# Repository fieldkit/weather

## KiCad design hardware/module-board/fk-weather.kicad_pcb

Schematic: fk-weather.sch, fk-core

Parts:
BT1: BATTERY_CELL; BAT_CR1210
C1, C2: 18pF; CAP-0603
C3, C4, C6, C7, C8, C13, C16, C18, C20: 100nF; CAP-0603
C5, C11, C12: 1uF; CAP-0603
C9, C14: 4.7uF; CAP-0603
C10: 4.7nF; CAP-0603
C15, C21: 10uF; CAP-0603
C17, C19: 10nF; CAP-0603
D1: Green; LED-0603
D4: PRTR5V0U2X; SOT-143B
D5: Orange; LED-0603
D6, D7, D8, D9, D10, D11: DIODE; SOD-123
F1: MF-PSMF050X-2; MF-PSMF020X
J1: MICRO-USB; USB_1051330011
J2, J7: CONN_01x05; Molex_CLIK-Mate_502382-0570_1x05_P1.25mm_Vertical
J3: CONN_01x03_SERIAL; Molex_CLIK-Mate_502382-0370_1x03_P1.25mm_Vertical
J4: CONN_01x04; Molex_CLIK-Mate_502382-0470_1x04_P1.25mm_Vertical
J5: MICRO-USB; USB_10118193-0001LF-core-mod
J6: CONN_02x05_SWD; HDR_02x05_Pitch1.27mm_SMD_SWD
J8: CONN_01x04; BM04B-SRSS-TB
J9, J12: CONN_01x02; SJ_OPEN
J10, J11: CONN_01x06; WURTH_615006138421
L1, L2: BLM18KG221SN1D; IND-0603
M1, M2, M3, M4: MOUNT_HOLE; HOLE_NPTH_2.7MM
Q4: 2N7002LT1G; SOT-23
R1, R22, R23, R30, R31, R32, R33: 1K; RES-0603
R2, R9: 330R; RES-0603
R3, R17: 2k2; RES-0603
R4, R5, R12: 10K; RES-0603
R6, R7, R16, R18, R19, R20, R34: 4.7K; RES-0603
R8, R14, R15: 100K; RES-0603
R10: 1M; RES-0603
R11, R13: ?; RES-0603
SW1: SPNO; SW_SPST_WURTH_1
U1: ATSAMD21G18A-AU; TQFP-48_7x7mm_Pitch0.5mm
U2: MCP1700T-3302E/MB; SOT-89
U3: TPS2052B; SOIC-8-N
U4: S25FL116K0XMFI041; SOIC-8-N-WIDE
U5: SK6812
U6: PCF8523; SOIC-8-N
Y1, Y2: FC-135; ABS07

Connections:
3V3: C3.1, C7.1, C8.1, C12.1, C16.1, C17.1, D1.2 (A), D5.2 (A), J2.1, J4.1, J6.1, J7.1, J8.2, J9.1, J12.1, L2.2, R1.1, R4.1, R5.2, R6.2, R7.2, R8.1, R12.2, R16.2, R18.2, R19.2, R20.2, U1.17 (VDDIO), U1.36 (VDDIO), U1.44 (VDDIN), U2.3 (VOUT), U3.2, U5.3 (VDD), U6.8 (VDD)
5V0: C9.1, C11.1, L1.1, U2.2 (VIN)
/A0: U1.3 (PA02)
/A1_WIND_DIR: D8.1 (K), D9.2 (A), R30.2, R34.2, U1.7 (PB08)
/A3: U1.9 (PA04), U5.2 (DI)
/A4: U1.10 (PA05)
/A5: U1.47 (PB02)
/ATN: U1.22 (PA13)
/D0: U1.16 (PA11)
/D1: U1.15 (PA10)
/D2: U1.23 (PA14)
/D5_FLASH_CS: U1.24 (PA15), U4.1 (~CS~)
/D6_RAIN: D6.2 (A), D7.1 (K), R32.2, U1.29 (PA20)
/D7_WEATHER_EN: R11.1, U1.30 (PA21), U3.3
/D8_PERIPH_EN: R13.1, U1.11 (PA06), U3.4
/D9: U1.12 (PA07)
/D10_WIND_SPEED: D10.2 (A), D11.1 (K), R33.2, U1.27 (PA18)
/D12: U1.28 (PA19)
/D13: Q4.1 (G), U1.26 (PA17)
/D30: J3.3 (D30), U1.37 (PB22)
/D31: J3.2 (D31), U1.38 (PB23)
/MISO: U1.21 (PA12), U4.2 (SO/IO1)
/MOSI: U1.19 (PB10), U4.5 (SI/IO0)
/PERIPH_3V3: C18.1, C20.1, C21.1, J9.2, R14.1, U3.6, U4.3 (~WP~/IO2), U4.7 (~HOLD~/IO3), U4.8 (VCC)
/RAIN_2: J10.2
/RAIN_5: J10.5
/RESET: R2.1, U1.40 (RESETN)
/RST: J6.10, R2.2, R4.2, SW1.2; also elsewhere on the board
/RX_LED: U1.48 (PB03)
/SCK: U1.20 (PB11), U4.6 (SCLK)
/SCL1: J4.3, J8.4, R7.1, R20.1, U1.32 (PA23), U6.6 (SCL)
/SCL2: J2.4, J7.4, R18.1, U1.14 (PA09)
/SDA1: J4.4, J8.3, R6.1, R19.1, U1.31 (PA22), U6.5 (SDA)
/SDA2: J2.5, J7.5, R16.1, U1.13 (PA08)
/SWCLK: J6.4, U1.45 (PA30)
/SWDIO: J6.2, U1.46 (PA31)
/TX_LED: U1.39 (PA27)
/USB+: D4.2, J1.3 (D+), J5.3 (D+), U1.34 (PA25)
/USB-: D4.3, J1.2 (D-), J5.2 (D-), U1.33 (PA24)
/USB_ID: R9.2, U1.41 (PA28)
/WEATHER_3V3: C13.1, C15.1, D6.1 (K), D9.1 (K), D10.1 (K), J12.2, R15.1, R34.1, U3.7
GND: BT1.2 (-), C1.1, C2.1, C3.2, C4.2, C5.2, C6.2, C7.2, C8.2, C9.2, C10.2, C11.2, C12.2, C13.2, C14.2, C15.2, C16.2, C17.2, C18.2, C19.2, C20.2, C21.2, D4.1, D7.2 (A), D8.2 (A), D11.2 (A), J1.5 (GND), J2.2, J3.1 (GND), J4.2, J5.5 (GND), J6.3, J6.5, J6.9, J7.2, J8.1, Q4.2 (S), R3.2, R10.2, R11.2, R13.2, R14.2, R15.2, R22.2, R23.2, R31.2, SW1.1, U1.5 (GNDANA), U1.18 (GND), U1.35 (GND), U1.42 (GND), U2.1 (GND), U3.1, U4.4 (VSS), U5.1 (GND), U6.4 (VSS); also elsewhere on the board
unnamed: BT1.1 (+), U6.3 (VBAT)
unnamed: C1.2, U1.2 (PA01), Y1.1
unnamed: C2.2, U1.1 (PA00), Y1.2
unnamed: C4.1, L2.1, U1.6 (VDDANA)
unnamed: C5.1, U1.43 (VDDCORE)
unnamed: C10.1, J1.6 (SHIELD), J5.7 (SHIELD), R10.1
unnamed: C6.1, C14.1, U1.4 (PA03)
unnamed: C19.1, R1.2
unnamed: D1.1 (K), R3.1
unnamed: D5.1 (K), R17.1
unnamed: F1.1, L1.2
unnamed: J1.4 (ID), J5.4 (ID), R8.2, R9.1
unnamed: J10.3, R23.1
unnamed: J10.4, R32.1
unnamed: J11.2, R22.1
unnamed: J11.3, R31.1
unnamed: J11.4, R33.1
unnamed: J11.5, R30.1
unnamed: Q4.3 (D), R17.2
unnamed: R5.1, U3.8
unnamed: R12.1, U3.5
unnamed: U6.1 (XI), Y2.2
unnamed: U6.2 (XO), Y2.1
VUSB: D4.4, F1.2, J1.1 (VBUS), J5.1 (VBUS)

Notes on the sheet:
TX0
RX0
32.768kHz
12.5pF
USB / POWER MANAGEMENT
LEDs
MCU
I2C
EXTERNAL SENSOR
RAIN
WIND
RTC
MOUNTING
FLASH
CORE CONNECTOR
EXTERNAL SERIAL
PERIPHERALS

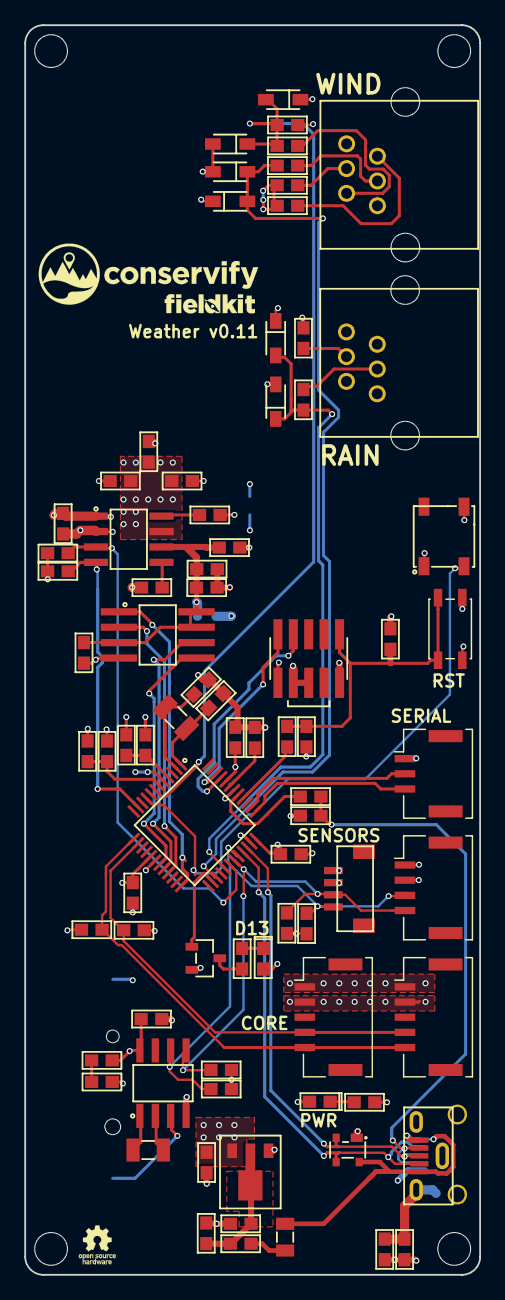
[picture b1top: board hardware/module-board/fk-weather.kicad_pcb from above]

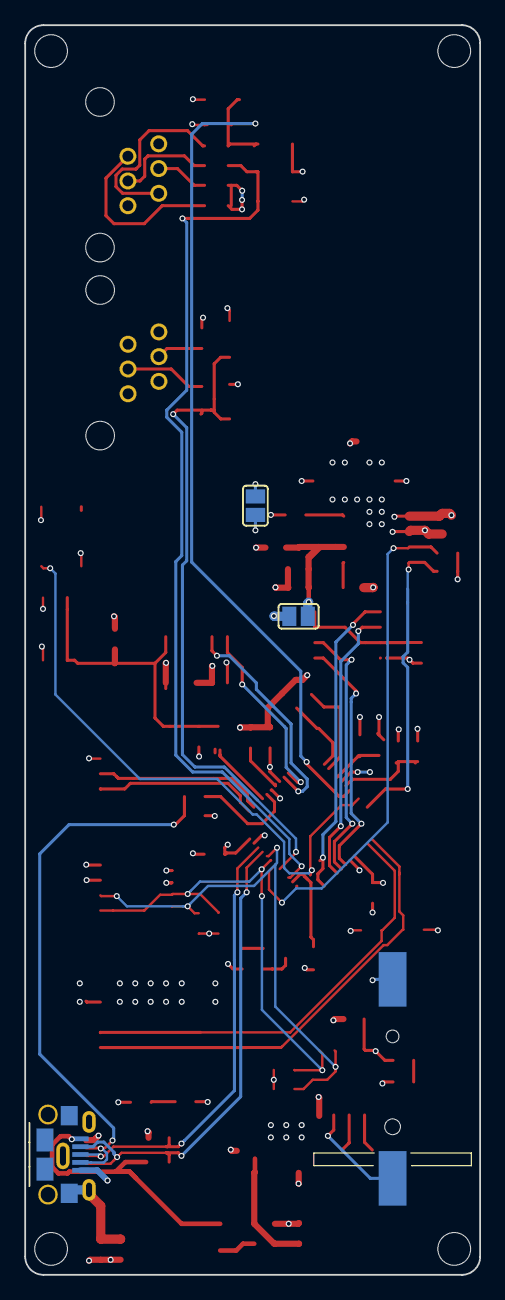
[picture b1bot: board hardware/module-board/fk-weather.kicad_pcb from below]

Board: 4 copper layers, 37.5 x 103.0 mm, 88 parts (4 on the bottom side), 53 nets.

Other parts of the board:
C22: 100nF; CAP-0603

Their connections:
/RST: C22.1; also elsewhere on the board
GND: C22.2; also elsewhere on the board

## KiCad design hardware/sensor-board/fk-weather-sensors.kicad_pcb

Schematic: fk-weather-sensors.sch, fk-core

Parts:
C1, C2, C5: 100nF; CAP-0603
C3: 1uF; CAP-0603
C4: 10uF; CAP-0603
J1: CONN_01x04; Molex_CLIK-Mate_502382-0470_1x04_P1.25mm_Vertical
U1: MPL3115A2; DFN-8-1EP_5x2.55mm_Pitch1.25mm_98ASA002260D
U2: TSL2591
U3: SHT31; SHT3x

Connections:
3V3: C2.1, C3.1, C4.1, C5.1, J1.1, U1.1 (VDD), U1.4 (VDDIO), U2.5 (VDD), U3.5 (VDD), U3.6 (nRESET)
/SCL: J1.3, U1.8 (SCL), U2.1 (SCL), U3.4 (SCL)
/SDA: J1.4, U1.7 (SDA), U2.6 (SDA), U3.1 (SDA)
GND: C1.2, C2.2, C3.2, C4.2, C5.2, J1.2, U1.3 (GND), U2.3 (GND), U3.2 (ADDR), U3.7 (R), U3.8 (GND), U3.PAD (GND)
unnamed: C1.1, U1.2 (CAP)

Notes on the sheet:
CONNECTOR
TSL (LIGHT)
SHT31 (TEMP)
MPL3115A2 (PRESSURE/HUMIDITY)

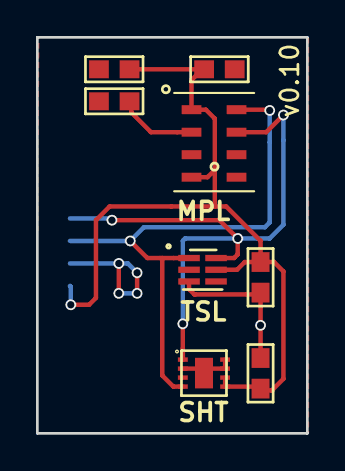
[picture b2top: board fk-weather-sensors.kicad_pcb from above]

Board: 2 copper layers, 15.0 x 22.0 mm, 9 parts (1 on the bottom side), 5 nets.

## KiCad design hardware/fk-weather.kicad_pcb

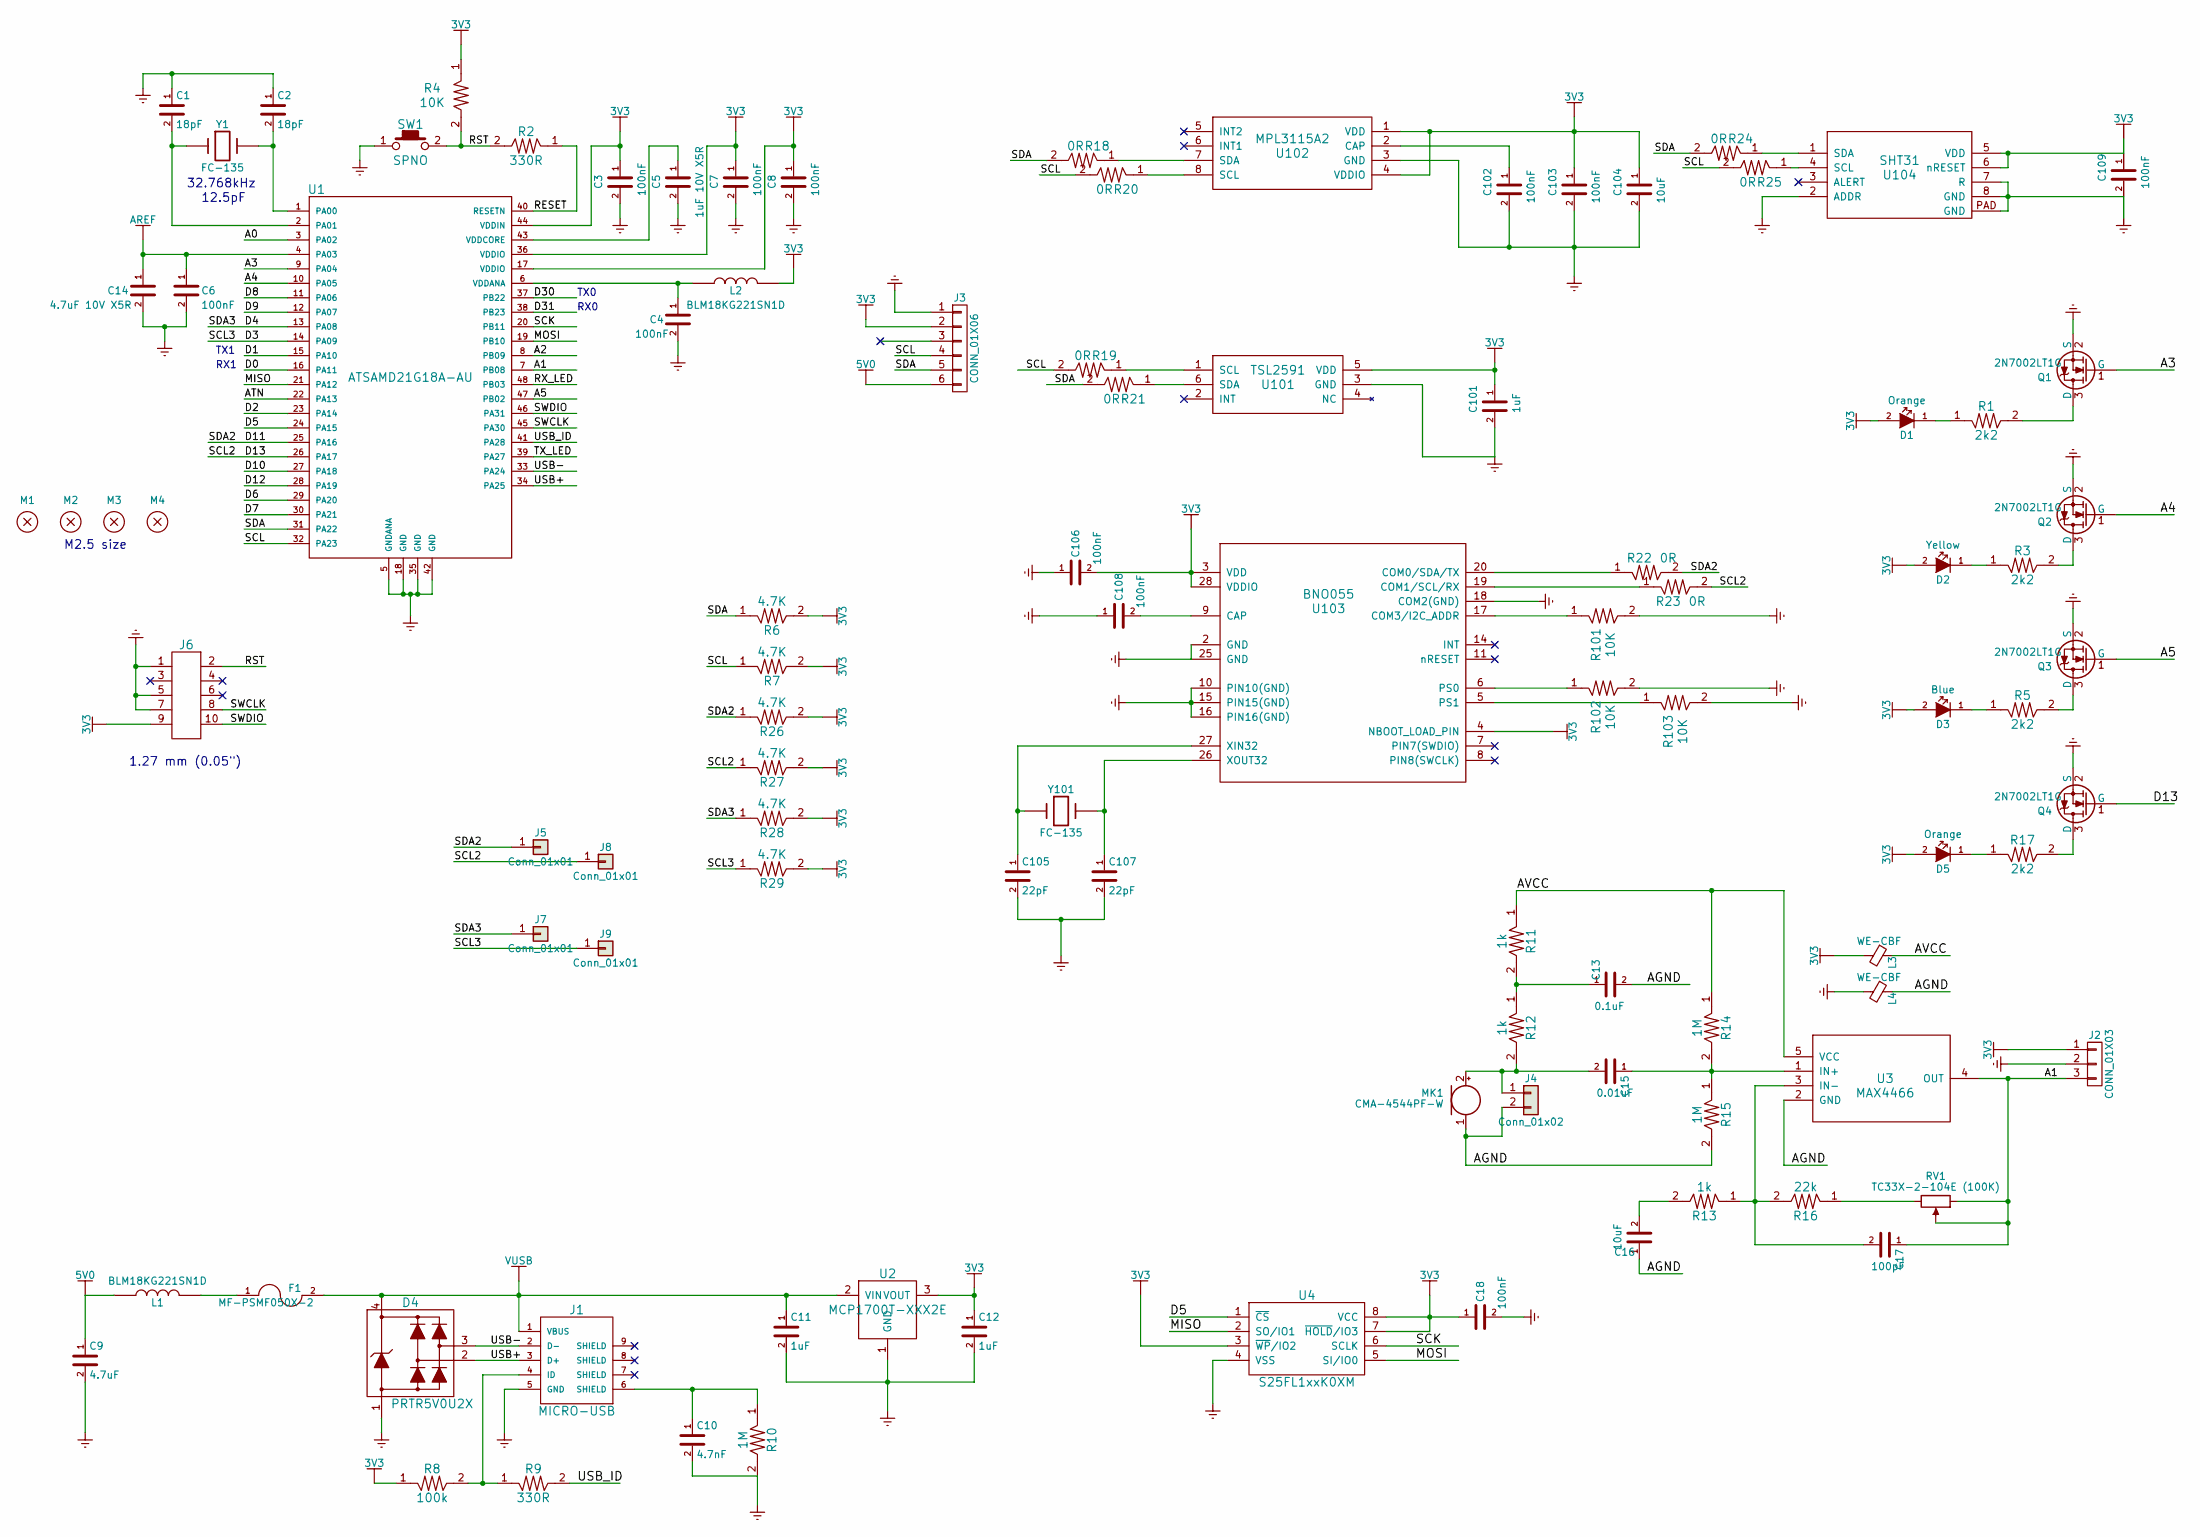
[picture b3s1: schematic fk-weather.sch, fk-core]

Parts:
C1, C2: 18pF; C_0603_HandSoldering
C3, C4, C6, C7, C8, C18, C102, C103, C106, C108, C109: 100nF; C_0603_HandSoldering
C5: 1uF 10V X5R; C_0603_HandSoldering
C9: 4.7uF; C_0603_HandSoldering
C10: 4.7nF; C_0603_HandSoldering
C11, C12, C101: 1uF; C_0603_HandSoldering
C13: 0.1uF; C_0603_HandSoldering
C14: 4.7uF 10V X5R; C_0603_HandSoldering
C15: 0.01uF; C_0603_HandSoldering
C16, C104: 10uF; C_0603_HandSoldering
C17: 100pF; C_0603_HandSoldering
C105, C107: 22pF; C_0603_HandSoldering
D1, D5: Orange; LED-0603
D2: Yellow; LED-0603
D3: Blue; LED-0603
D4: PRTR5V0U2X; SOT-143B
F1: MF-PSMF050X-2; MF-PSMF020X
J1: MICRO-USB
J2: CONN_01X03; Socket_Strip_Straight_1x03_Pitch2.54mm
J3: CONN_01X06; Socket_Strip_Straight_1x06_Pitch2.54mm
J4: Conn_01x02; Socket_Strip_Straight_2x01_Pitch2.54mm
J5, J7, J8, J9: Conn_01x01; Measurement_Point_Round-SMD-Pad_Small
J6: CONN-HDR-2x5; Socket_Strip_Straight_2x05_Pitch1.27mm_SMD
L1, L2: BLM18KG221SN1D; L_0603_HandSoldering
L3, L4: WE-CBF; R_0603_HandSoldering
M1, M2, M3, M4: MOUNT_HOLE; HOLE_NPTH_2.2MM
MK1: CMA-4544PF-W; Socket_Strip_Straight_1x02_Pitch2.54mm
Q1, Q2, Q3, Q4: 2N7002LT1G; SOT-23
R1, R3, R5, R17: 2k2; R_0603_HandSoldering
R2, R9: 330R; R_0603_HandSoldering
R4, R101, R102, R103: 10K; R_0603_HandSoldering
R6, R7, R26, R27, R28, R29: 4.7K; R_0603_HandSoldering
R8: 100k; R_0603_HandSoldering
R10, R14, R15: 1M; R_0603_HandSoldering
R11, R12, R13: 1k; R_0603_HandSoldering
R16: 22k; R_0603_HandSoldering
R18, R19, R20, R21, R22, R23, R24, R25: 0R; SJ_SHORTED
RV1: TC33X-2-104E (100K); BOURNS-TC33X-2
SW1: SPNO; TS-018
U1: ATSAMD21G18A-AU; TQFP-48_7x7mm_Pitch0.5mm
U2: MCP1700T-XXX2E; SOT-89
U3: MAX4466; SC70-5
U4: S25FL1xxK0XM; SOIC-8-N
U101: TSL2591; DFN-6-1EP_2x2mm_Pitch0.65mm
U102: MPL3115A2; DFN-8-1EP_5x2.55mm_Pitch1.25mm_98ASA002260D
U103: BNO055
U104: SHT31; SHT3x
Y1, Y101: FC-135; ABS07

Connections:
3V3: C3.1, C7.1, C8.1, C12.1, C18.1, C101.1, C103.1, C104.1, C106.2, C109.1, D1.2 (A), D2.2 (A), D3.2 (A), D5.2 (A), J2.1, J3.2, J6.9, L2.2, L3.2, R4.1, R6.2, R7.2, R8.1, R26.2, R27.2, R28.2, R29.2, U1.17 (VDDIO), U1.36 (VDDIO), U1.44 (VDDIN), U2.3 (VOUT), U4.3 (~WP~/IO2), U4.7 (~HOLD~/IO3), U4.8 (VCC), U101.5 (VDD), U102.1 (VDD), U102.4 (VDDIO), U103.3 (VDD), U103.4 (NBOOT_LOAD_PIN), U103.28 (VDDIO), U104.5 (VDD), U104.6 (nRESET)
5V0: C9.1, J3.6, L1.1
/A0: U1.3 (PA02)
/A1: C17.1, J2.3, RV1.1, RV1.2, U1.7 (PB08), U3.4 (OUT)
/A2: U1.8 (PB09)
/A3: Q1.1 (G), U1.9 (PA04)
/A4: Q2.1 (G), U1.10 (PA05)
/A5: Q3.1 (G), U1.47 (PB02)
/AGND: C13.2, C16.1, J4.2, L4.1, MK1.1 (-), R15.2, U3.2 (GND)
/ATN: U1.22 (PA13)
/AVCC: L3.1, R11.1, R14.1, U3.5 (VCC)
/D0: U1.16 (PA11)
/D1: U1.15 (PA10)
/D2: U1.23 (PA14)
/D3: J9.1, R29.1, U1.14 (PA09)
/D4: J7.1, R28.1, U1.13 (PA08)
/D5: U1.24 (PA15), U4.1 (~CS~)
/D6: U1.29 (PA20)
/D7: U1.30 (PA21)
/D8: U1.11 (PA06)
/D9: U1.12 (PA07)
/D10: U1.27 (PA18)
/D11: J5.1, R22.2, R26.1, U1.25 (PA16)
/D12: U1.28 (PA19)
/D13: J8.1, Q4.1 (G), R23.2, R27.1, U1.26 (PA17)
/D30: U1.37 (PB22)
/D31: U1.38 (PB23)
/MISO: U1.21 (PA12), U4.2 (SO/IO1)
/MOSI: U1.19 (PB10), U4.5 (SI/IO0)
/RESET: R2.1, U1.40 (RESETN)
/RST: J6.2, R2.2, R4.2, SW1.2
/RX_LED: U1.48 (PB03)
/SCK: U1.20 (PB11), U4.6 (SCLK)
/SCL: J3.4, R7.1, R19.2, R20.2, R25.2, U1.32 (PA23)
/SDA: J3.5, R6.1, R18.2, R21.2, R24.2, U1.31 (PA22)
/SWCLK: J6.8, U1.45 (PA30)
/SWDIO: J6.10, U1.46 (PA31)
/TX_LED: U1.39 (PA27)
/USB+: D4.2, J1.3 (D+), U1.34 (PA25)
/USB-: D4.3, J1.2 (D-), U1.33 (PA24)
/USB_ID: R9.2, U1.41 (PA28)
AREF: C6.1, C14.1, U1.4 (PA03)
GND: C1.1, C2.1, C3.2, C4.2, C5.2, C6.2, C7.2, C8.2, C9.2, C10.2, C11.2, C12.2, C14.2, C18.2, C101.2, C102.2, C103.2, C104.2, C105.2, C106.1, C107.2, C108.1, C109.2, D4.1, J1.5 (GND), J2.2, J3.1, J6.1, J6.5, J6.7, L4.2, Q1.2 (S), Q2.2 (S), Q3.2 (S), Q4.2 (S), R10.2, R101.2, R102.2, R103.2, SW1.1, U1.5 (GNDANA), U1.18 (GND), U1.35 (GND), U1.42 (GND), U2.1 (GND), U4.4 (VSS), U101.3 (GND), U102.3 (GND), U103.2 (GND), U103.10 (PIN10(GND)), U103.15 (PIN15(GND)), U103.16 (PIN16(GND)), U103.18 (COM2(GND)), U103.25 (GND), U104.2 (ADDR), U104.7 (R), U104.8 (GND), U104.PAD (GND)
unnamed: C1.2, U1.2 (PA01), Y1.1
unnamed: C2.2, U1.1 (PA00), Y1.2
unnamed: C4.1, L2.1, U1.6 (VDDANA)
unnamed: C5.1, U1.43 (VDDCORE)
unnamed: C10.1, J1.6 (SHIELD), R10.1
unnamed: C13.1, R11.2, R12.1
unnamed: C15.1, R14.2, R15.1, U3.1 (IN+)
unnamed: C15.2, J4.1, MK1.2 (+), R12.2
unnamed: C16.2, R13.2
unnamed: C17.2, R13.1, R16.2, U3.3 (IN-)
unnamed: C102.1, U102.2 (CAP)
unnamed: C105.1, U103.27 (XIN32), Y101.1
unnamed: C107.1, U103.26 (XOUT32), Y101.2
unnamed: C108.2, U103.9 (CAP)
unnamed: D1.1 (K), R1.1
unnamed: D2.1 (K), R3.1
unnamed: D3.1 (K), R5.1
unnamed: D5.1 (K), R17.1
unnamed: F1.1, L1.2
unnamed: J1.4 (ID), R8.2, R9.1
unnamed: Q1.3 (D), R1.2
unnamed: Q2.3 (D), R3.2
unnamed: Q3.3 (D), R5.2
unnamed: Q4.3 (D), R17.2
unnamed: R16.1, RV1.3
unnamed: R18.1, U102.7 (SDA)
unnamed: R19.1, U101.1 (SCL)
unnamed: R20.1, U102.8 (SCL)
unnamed: R21.1, U101.6 (SDA)
unnamed: R22.1, U103.20 (COM0/SDA/TX)
unnamed: R23.1, U103.19 (COM1/SCL/RX)
unnamed: R24.1, U104.1 (SDA)
unnamed: R25.1, U104.4 (SCL)
unnamed: R101.1, U103.17 (COM3/I2C_ADDR)
unnamed: R102.1, U103.6 (PS0)
unnamed: R103.1, U103.5 (PS1)
VUSB: C11.1, D4.4, F1.2, J1.1 (VBUS), U2.2 (VIN)

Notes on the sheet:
TX0
RX0
RX1
TX1
M2.5 size
1.27 mm (0.05")
32.768kHz
12.5pF

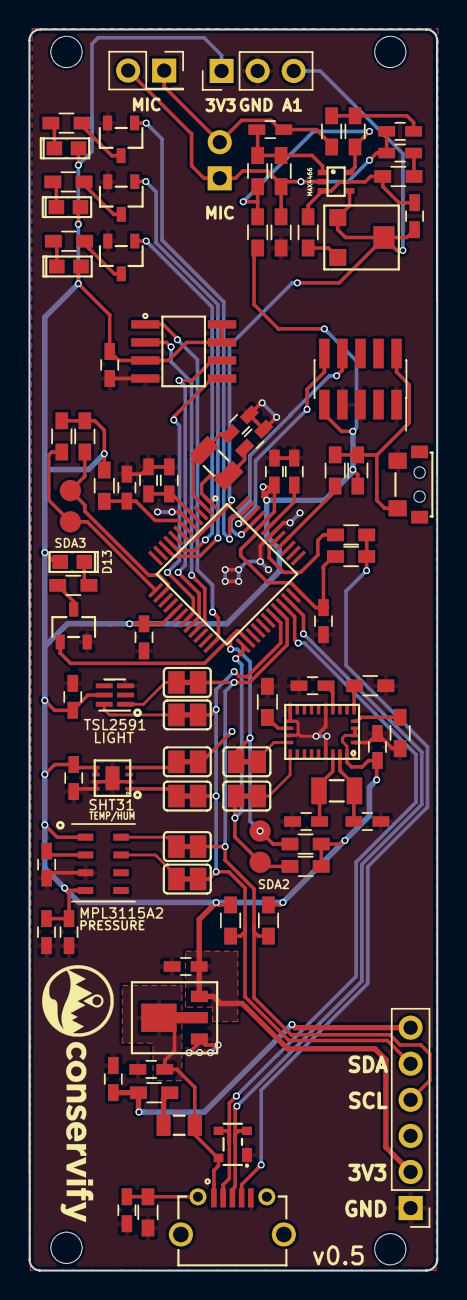
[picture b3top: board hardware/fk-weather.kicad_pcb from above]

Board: 2 copper layers, 28.7 x 87.4 mm, 99 parts (1 on the bottom side), 64 nets.

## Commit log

2017-03-13 First commit.
2017-03-23 Don't commit firmwaretool.properties
2017-04-01 Read outside temperature from an attached DHT22
2017-07-25 Starting on the basic sensor module board. Just IC stuff.
2017-07-26 Adding pull ups, fixing the outline. Plotting.
2017-07-26 Adding USB connector and 3v3 regulator.
2017-07-26 Adding MAX4466.
2017-07-26 Fix part for ferrite beads, replot.
2017-08-18 Fixing footprints for light and pressure.
2017-08-18 Collecting datasheets.
2017-08-23 Fixing USB oval drills.
2017-08-23 Arranging labels for printing out an assembly map.
2017-08-24 Working on layout issues, trying to figure out the MCU problem.
    Also broke up power from USB.
2017-09-12 Export new gerbers.
2017-09-14 Programming header was wrong from the SMD switch.
2017-09-15 Adding an LED to D13
2017-09-15 Removing extraneous headers.
2017-09-15 Adding a header for an LED.
2017-09-15 Nudge button over.
2017-09-27 Wire ADDR on SHT31 to GND.
2017-10-02 Some parts.
2017-11-02 Add way to isolate sensors in from the bus in testing.
2017-11-02 Testing firmware.
2017-11-02 Separate I2C for BNO055, also break a third out for fk-core.
2017-11-03 New gerbers.
2017-11-17 Using a better SHT3x footprint.
2017-11-17 Test firmware that runs through all the devices.
2017-11-17 Fixing up some parts to work with our BOM scripts.
2017-11-27 Adding flash memory to the schematic.
2017-11-28 Make build work like atlas repository.
2017-11-28 Adding flash memory to PCB. Plotting.
2017-11-29 Rounding corners of the PCB.
2017-12-04 Re-use Makefile patterns.
2017-12-08 Fix version number.
2017-12-18 Add SHT31 library for testing.
2017-12-20 Rename to main.cpp
2017-12-20 Add flash memory to firmware test.
2017-12-20 Adding another breakout for the MIC to attach a header to for probing.
2017-12-20 Make fab labels easier to read.
2017-12-21 Reading sensor data. Also some basic analog sampling code.
2017-12-21 Nuking old weather code.
2017-12-22 Starting on the module side of things.
2017-12-22 Actually fill in module sensor readings.
2017-12-22 Use new module status return for backoff.
    This tells core to give us some time to ourselves so we can use the I2C
    bus to talk to *our* sensors.
2017-12-24 Start after a few seconds waiting for USB Serial.
2017-12-24 Add watchdog to main loop.
2017-12-24 Setup watchdog (to setup the leds)
2017-12-27 Add AtSamd library.
2017-12-27 Adding max1704x library.
2017-12-27 Renaming max1704x library to FuelGauge.
2017-12-28 Hardware will becoem two boards. Make dir.
2017-12-28 Will regenerate these.
2017-12-28 Adding PCB/sch for the wind/rain connectors.
2017-12-28 First pass on the sensor board.
2017-12-28 Removing sensors from module board.
2017-12-28 Wire up the I2C buses to the header.
2017-12-28 Fix RJ11 jacks. Clean up the board and I2C lines.
    Got rid of the solder jumpers and just broke both out.
2017-12-28 Expose Serial2 (D31/D30)
2017-12-28 Change header orien. Plot.
2017-12-29 PCB labels for D30/D31
2017-12-30 Watchdog moved into Module.
2017-12-31 Adding TinyGPS library.
2017-12-31 Change to PendingReading struct.
2017-12-31 Record elapsed time.
2018-01-06 Change version to 0.6.
2018-01-11 Pass which TwoWire to use for core comms.
2018-01-12 Set time on readings.
2018-01-12 Gerbers
2018-01-18 Add data-protocol dependency.
2018-01-20 Using the prettier footprints for some passives.
2018-01-22 Fix TSL2591 footprint.
2018-01-23 First pass at the weather meters firmware.
2018-01-23 Separating files up, moving test/module firmware code into common.
2018-01-23 Integrating the WeatherMeters into the module firmware.
2018-01-23 Bugfix, using the same variable twice.
2018-01-23 Fix number of sensors.
2018-01-23 Using secondary I2C for core communications.
2018-01-23 Initialize the sensors at startup.
2018-01-24 Adding debugfpln to test firmware.
2018-01-24 Save persisted state into SerialFlash.
    This ensures our long term values don't get erased and that they stay
    consistent. Especially due to our stability issues on I2C now.
2018-01-24 Only save if state changes.
2018-01-24 Fix persisted save saving. Also uses a lower level mechanism.
2018-01-24 Store counters too, this way we know when a day is up, etc...
2018-01-25 Moving FlashStorage to a separate file.
2018-01-25 FlashStorage alternates between two blocks.
    This is so that we have a value to fall back on if we happen to be
    interrupted during a write.
2018-01-25 Only save every 10s.
2018-02-05 Format specifier fix.
2018-02-13 Use adafruit ASFcore
2018-02-15 Plotting new gerbers. Bump version.
2018-02-16 Use forked WiFi101 library.
2018-02-16 Moving FlashStorage class to firmware common.
2018-03-02 Drop daily values, add previous hour of rain and hourly wind gust.
    The idea of a day is awkward in the context of the station because we don't
    necessarily know the time zone, etc... So it's easier to build daily
    values after the fact from hourly information.
    Also, having previous hour is good because that's probably a more accurate
    value than using some arbitrary sample in the current hour.
2018-03-02 Sync our "dumb" clock to the actual time when that's set.
2018-03-02 Change startup order to setup Watchdog earlier.
    I noticed something hang, probably during scanning for weather sensors and
    hopefully with the earlier watchdog startup we can restart and get out.
2018-03-05 Using key names for sensors. Going to pretty up using metadata.
2018-03-21 Bump revision. Nudge some parts.
2018-03-21 Use Zero RTC for our "meters clock" instead of managing our own.
    The idea here is that this will meant he weather meter data is nearly
    always synced to the proper time. Even in the rare cases where we're
    confused about the time. Hell, once we get a time the time is usually
    correct from then on.
2018-03-23 Don't try and read other sensors that we can't find.
2018-03-27 New logging interface.
2018-04-03 Set module type.
2018-04-19 Use taskQueue for sensor task.
2018-04-27 Add lwstreams dependency.
2018-04-27 Project name, disable verbose makefile.
2018-05-01 Migrate to arduino-logging.
2018-05-07 Add NFET for peripherals. In this case just the flash.
2018-05-21 Updating BOM details.
2018-06-13 Cleanup.
2018-06-27 Add phylum dependency.
2018-07-01 Use new phylum flash storage that wanders over all available blocks.
2018-07-03 Add dimensions.
2018-07-03 Add connectors. Clean up mounting hole locations.
2018-07-06 Adding high side switch for peripherals.
2018-07-10 Plotting gerbers.
2018-07-13 Flash takes a Watchdog now. Add to meters.
2018-07-18 Easier to read labels.
2018-07-18 Better logging in test firmware. Enable peripherals.
2018-07-18 Enable peripherals on startup. Also kill them on fatal errors.
2018-07-20 Amazon build script.
2018-07-23 Drop large header. Add debug. Drop LEDs.
2018-07-23 Same size as Core board.
2018-07-23 Add RTC. Molex connector cleanup. Add RGB LED.Fix diode footprints.
2018-07-23 Add a second core port.
2018-07-24 Nudge holes to match Core pattern, which needed a little more room.
2018-07-24 Part for load switch was wrong, fixing.
2018-07-24 Add lwcron dependency.
2018-07-25 Pass firmware/build info in.
2018-07-25 Upgrade to Kicad 5.
2018-07-27 New USB for vertical entry.
2018-07-30 Use latest dependencies.
2018-07-30 Rename target.
2018-07-30 Fix a few small traces and the silkscreen.
2018-07-30 Add number of readings and module name to info.
2018-07-31 Use new allocation strategy for ModuleInfo.
2018-08-02 Ignore dependencies.cmake
2018-08-03 Add Jenkinsfile.
2018-08-08 Trigger distribution job.
2018-08-08 Getting things building after FSM changes.
2018-08-09 Not waiting on distribution build.
2018-08-09 Use helper for updating distribution site.
2018-08-11 Compile flags to enable flash in phylum.
2018-08-11 Incorporate separate FlashFS service.
2018-08-13 Compile flags for phylum.
2018-08-14 Add distribute step.
2018-08-15 Archive binaries.
2018-08-15 Library order to fix linker problem.
2018-08-18 Inherit from minimum state for modules (has firmware banks)
2018-08-20 Set firmware compiled time.
2018-08-20 Fix dependency path.
2018-08-21 Upgrade to new CMake module.
2018-08-21 Pass archive pathspec.
2018-08-21 Set firmware directory for distribution.
2018-08-22 Consistent part values across our schematics.
2018-08-22 Part updates.
2018-08-24 Use repository URLs for deps.
2018-08-24 Use tools name for dependencies.sd.
2018-08-24 Fix SK6812 and cleanup signal naming.
2018-08-24 Fix rescued stuff and clear DRC problems.
2018-08-28 Use state for readings instead of callbacks.
2018-08-28 Rename class to avoid collision.
2018-08-28 Use more compatible FP for flash.
2018-08-28 Schematic/FP cleanup. Nothing major.
2018-08-28 Consistency in part values
2018-08-28 Add NeoPixel dependency.
2018-09-07 Bump version and plot gerbers.
2018-09-20 Fix labels.
2018-09-24 Labels on sensor board.
2018-09-24 Better markings for easier placing on sensors.
2018-09-26 Pin to newer library versions.
2018-09-26 Add flag to control PCF8523, which weather modules have now.
2018-09-27 Get rid of extra date time field on weather state.
2018-09-27 Re-enable save/load of weather state.
2018-09-27 Quick fix for persistence issue, leave MinimumFlashState alone.
2018-09-27 Use the single, Module level instance of FlashState.
2018-09-27 Split module files up.
2018-09-27 No need for the load method anymore.
2018-09-27 Initialize WeatherServices static.
2018-10-04 Rename files to match naming style.
2018-10-04 Toggle peripherals in test and module.
2018-10-31 Open debug serial if USB is unavailable.
2018-11-01 Set required uptime parameter.
2018-11-07 Adding some pull downs.
2018-11-08 Fixing font sizes on schematic.
2018-11-19 Moving labels around.
2018-12-04 Add orientation indicator to SWD fp.
2018-12-04 Switch to 2.7mm mounting holes.
2018-12-04 Remove extra trace.
2018-12-11 Pull boards peripheral enable/disable into one location.
2018-12-12 Use new board definition style.
2018-12-12 Fix make jobserver warnings.
2018-12-20 Started replacing parts on the weather board, including the USB connectors and the switching component
2018-12-20 Swapped to 4 layer
2018-12-20 Finished v0.11, generated gerbers
2018-12-20 Added debounce capacitor and regenerated v0.11 gerbers
2018-12-20 Schematic cleanup
2019-01-02 Added 02x03 panelized version of the PCB for manufacture, including gerber files
2019-01-29 Regenerated gerbers.
2019-02-08 Clear up which readings are from where.
2019-02-08 Initialize serial flash persistence in the test.
2019-02-08 Rename a preprocessor define.
2019-02-08 No more false positives on SHT31 test.
2019-02-12 Mask reserved bits out of status.
2019-02-12 Get rid of extra debug/logging stuff and some cleanup in test.
2019-02-12 Use board wrapper to initialize.
2019-02-15 If check fails just gather wind meter data.
2019-02-15 Flash helper script.
2019-02-19 Archive test firmware.
2019-02-25 Upgrade nanopb.
2019-03-13 Fixed missing resistor values.
2019-03-15 Script to flash and test.
2019-03-21 Updating flash and test scripts.
2019-04-23 Use absolute BUILD in Makefile.
